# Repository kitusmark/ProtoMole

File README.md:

# ProtoMole - Permanent protoboard
the next step of prototiping. If you need your design somewhere more permanent, this is the protoboard to do it.

Sometimes I find myself wanting to have a circuit in a more fixed position, so I designed this permanent protoboard.

For now it's only in 5x5cm version but I'm planning to make a couple more sizes.

###Folders 

Protomole5 has the 5x5 cm version with all the gerber files and eagle originals.

##How It's done

+ 0,1" standard pitch so you can fit almost everything. 
+ Small 5x5cm format
+ Double power rails. It has solder jumpers at the rear so you can connect both rails.
+ 3,2mm mounting holes
+ Small holes in the middle for an easy and clean break
+ Pins labeled with letters and numbers
+ Cheap, small and useful!

##Some images

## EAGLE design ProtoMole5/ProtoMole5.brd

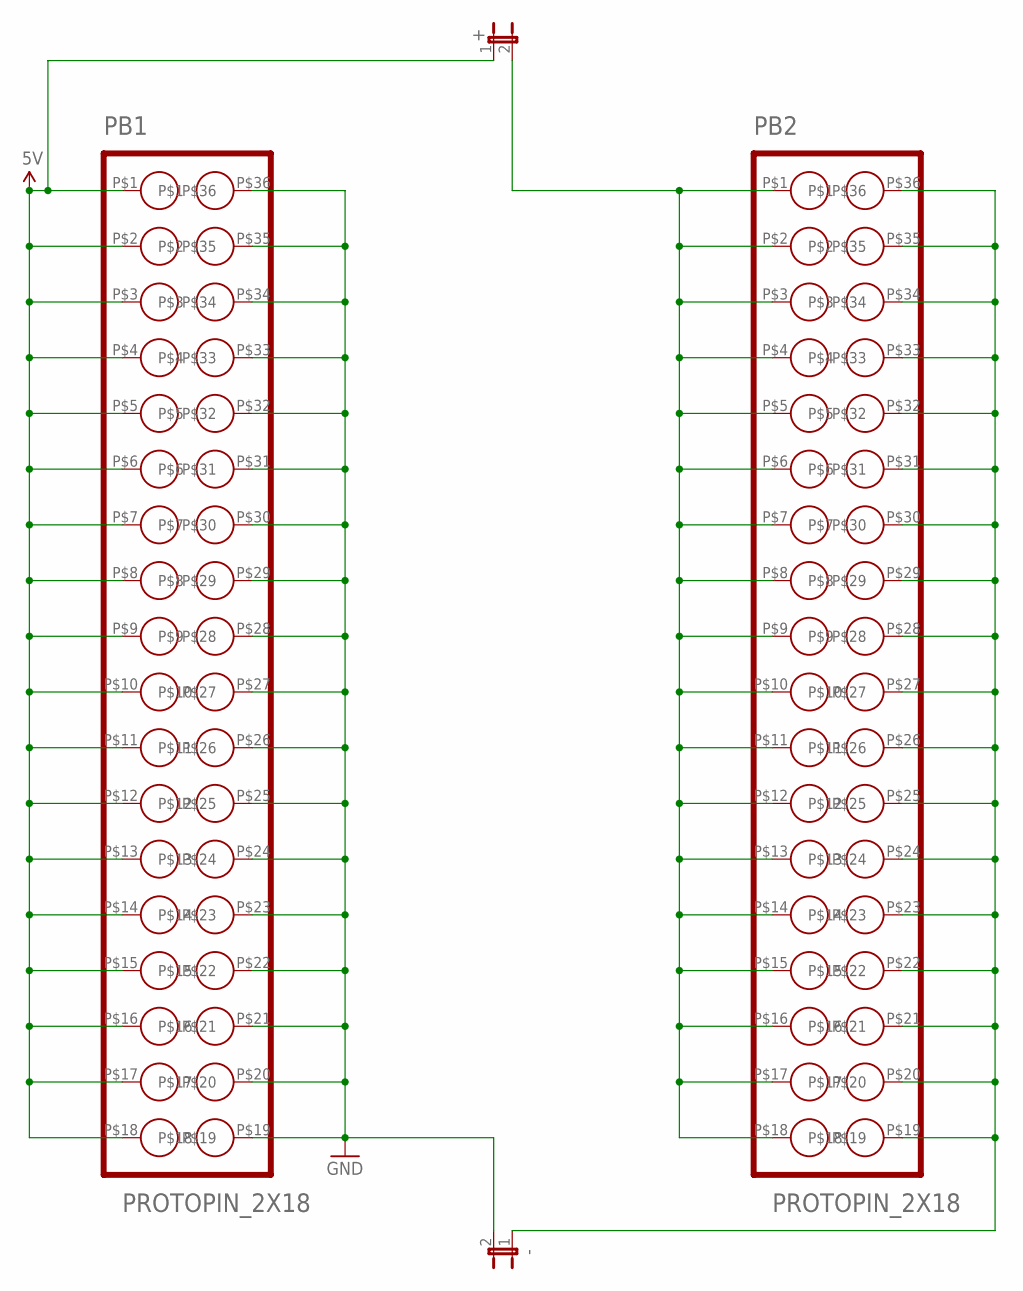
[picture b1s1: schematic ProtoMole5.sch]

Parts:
+: JUMPER-2SMD-NO-NS; SJ_2S-NO-NS
-: JUMPER-2SMD-NO-NS; SJ_2S-NO-NS
PB1, PB2: PROTOPIN_2X18; 2X18_PINHEADER

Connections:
5V: +.1, PB1.P$1, PB1.P$2, PB1.P$3, PB1.P$4, PB1.P$5, PB1.P$6, PB1.P$7, PB1.P$8, PB1.P$9, PB1.P$10, PB1.P$11, PB1.P$12, PB1.P$13, PB1.P$14, PB1.P$15, PB1.P$16, PB1.P$17, PB1.P$18
GND: -.2, PB1.P$19, PB1.P$20, PB1.P$21, PB1.P$22, PB1.P$23, PB1.P$24, PB1.P$25, PB1.P$26, PB1.P$27, PB1.P$28, PB1.P$29, PB1.P$30, PB1.P$31, PB1.P$32, PB1.P$33, PB1.P$34, PB1.P$35, PB1.P$36
unnamed: -.1, PB2.P$19, PB2.P$20, PB2.P$21, PB2.P$22, PB2.P$23, PB2.P$24, PB2.P$25, PB2.P$26, PB2.P$27, PB2.P$28, PB2.P$29, PB2.P$30, PB2.P$31, PB2.P$32, PB2.P$33, PB2.P$34, PB2.P$35, PB2.P$36
unnamed: +.2, PB2.P$1, PB2.P$2, PB2.P$3, PB2.P$4, PB2.P$5, PB2.P$6, PB2.P$7, PB2.P$8, PB2.P$9, PB2.P$10, PB2.P$11, PB2.P$12, PB2.P$13, PB2.P$14, PB2.P$15, PB2.P$16, PB2.P$17, PB2.P$18

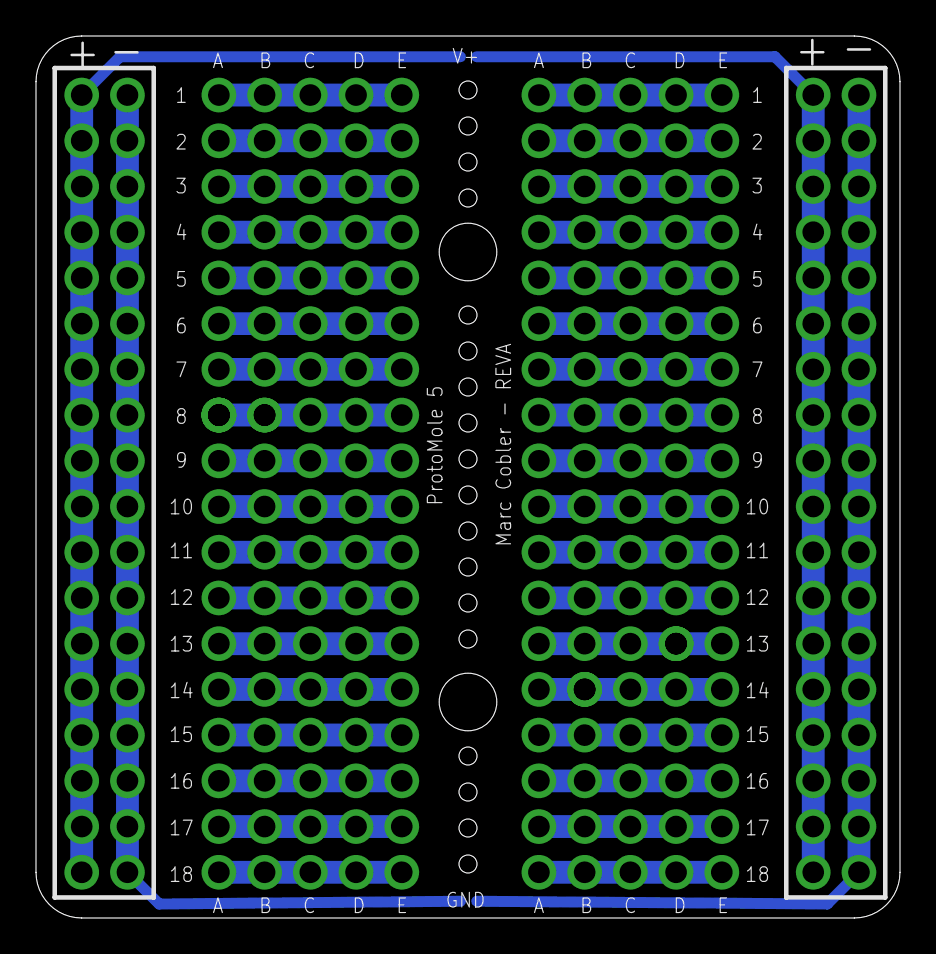
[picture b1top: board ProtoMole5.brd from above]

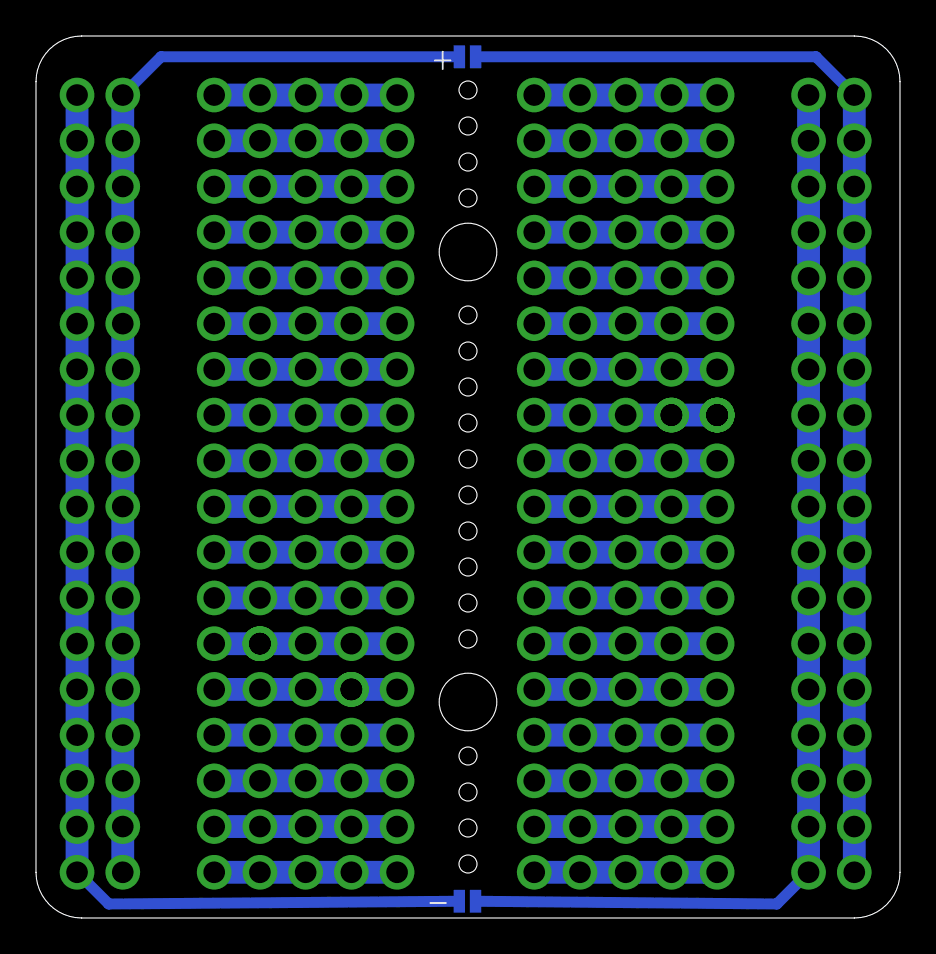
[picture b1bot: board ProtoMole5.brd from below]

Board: 2 copper layers, 48.0 x 49.0 mm, 4 parts (2 on the bottom side), 4 nets.

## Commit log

2016-01-28 Updated README and images!
2016-01-28 Correct directory of img's
2016-01-28 redo img directory
2016-01-28 updated image sizes
2016-01-28 resize
2016-02-01 Upload design files

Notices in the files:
parts and their libraries:
SparkFun-Retired: Licensing:Creative Commons ShareAlike 4.0 International - https://creativecommons.org/licenses/by-sa/4.0
